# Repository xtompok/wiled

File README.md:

# wiled
LED driver with wireless control

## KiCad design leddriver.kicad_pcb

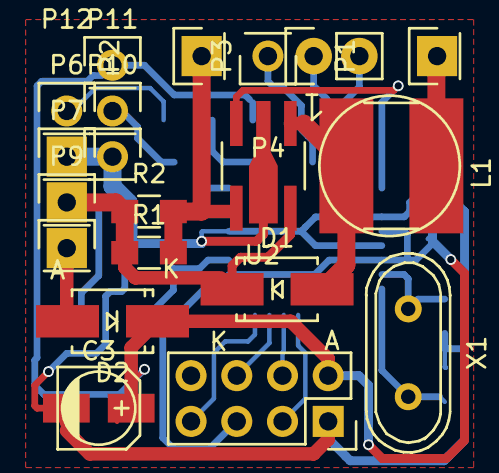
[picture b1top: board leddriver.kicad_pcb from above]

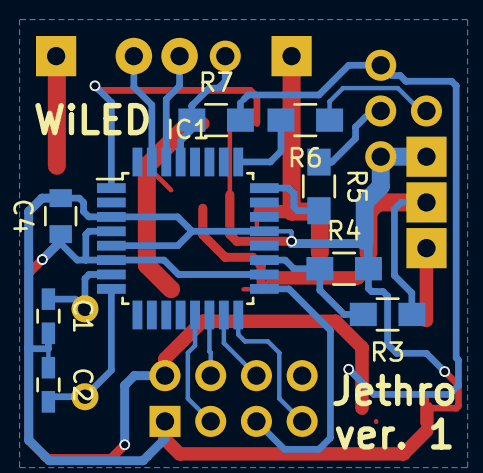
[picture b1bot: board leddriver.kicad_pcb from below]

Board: 2 copper layers, 29 parts (9 on the bottom side), 23 nets.

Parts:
C1, C2: 22p; C_0603_HandSoldering
C3: CP; c_elec_4x5.3
C4: 100n; C_0805
D1: D_Schottky; SMA_Handsoldering
D2: D; SMA_Handsoldering
IC1: ATMEGA88PA-A; TQFP-32_7x7mm_Pitch0.8mm
L1: INDUCTOR; DLG-0705
P1: LED-; Pin_Header_Straight_1x01
P2: LED+; Pin_Header_Straight_1x01
P3: USART; Pin_Header_Straight_1x02
P4: RST; Pin_Header_Straight_1x01
P5: NRF; Socket_Strip_Straight_2x04
P6, P10: BAT-; Pin_Header_Straight_1x01
P7: BAT+; Pin_Header_Straight_1x01
P9: U1/2; Pin_Header_Straight_1x01
P11, P12: IO; Pin_Header_Straight_1x01
P13: 3V3; Pin_Header_Straight_1x01
R1, R2: 0R33; R_0805_HandSoldering
R3: 100K; R_0805_HandSoldering
R4: 10K; R_0805_HandSoldering
R5, R6: 330; R_0805_HandSoldering
R7: 4k7; R_0805_HandSoldering
U2: PT4115; SOT89-5_Big_Pad_Handsoldering
X1: Crystal; Crystal_HC49-U_Vertical

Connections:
+3V3: C3.1, C4.1, D2.1, IC1.4, IC1.6, IC1.18, P5.2, P13.1, R7.2
+BATT: D1.1, P7.1, R1.1, R2.1, R3.1, U2.5
GND: C1.2, C2.1, C3.2, C4.2, IC1.3, IC1.5, IC1.21, P5.1, P6.1, P10.1, R4.2, U2.2
unnamed: C1.1, IC1.7, X1.1
unnamed: C2.2, IC1.8, X1.2
unnamed: D1.2, L1.2, U2.1
unnamed: D2.2, P9.1
unnamed: IC1.1, U2.3
unnamed: IC1.13, P5.3
unnamed: IC1.14, P5.4
unnamed: IC1.15, P5.6
unnamed: IC1.16, P5.7
unnamed: IC1.17, P5.5
unnamed: IC1.19, R3.2, R4.1
unnamed: IC1.24, R5.2
unnamed: IC1.25, R6.2
unnamed: IC1.29, P4.1, R7.1
unnamed: IC1.30, P3.1
unnamed: IC1.31, P3.2
unnamed: L1.1, P1.1
unnamed: P2.1, R1.2, R2.2, U2.4
unnamed: P11.1, R5.1
unnamed: P12.1, R6.1

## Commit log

2016-02-06 Added KiCAD files.
2016-02-26 Added first complete version and library.
2016-02-26 library for driver.
